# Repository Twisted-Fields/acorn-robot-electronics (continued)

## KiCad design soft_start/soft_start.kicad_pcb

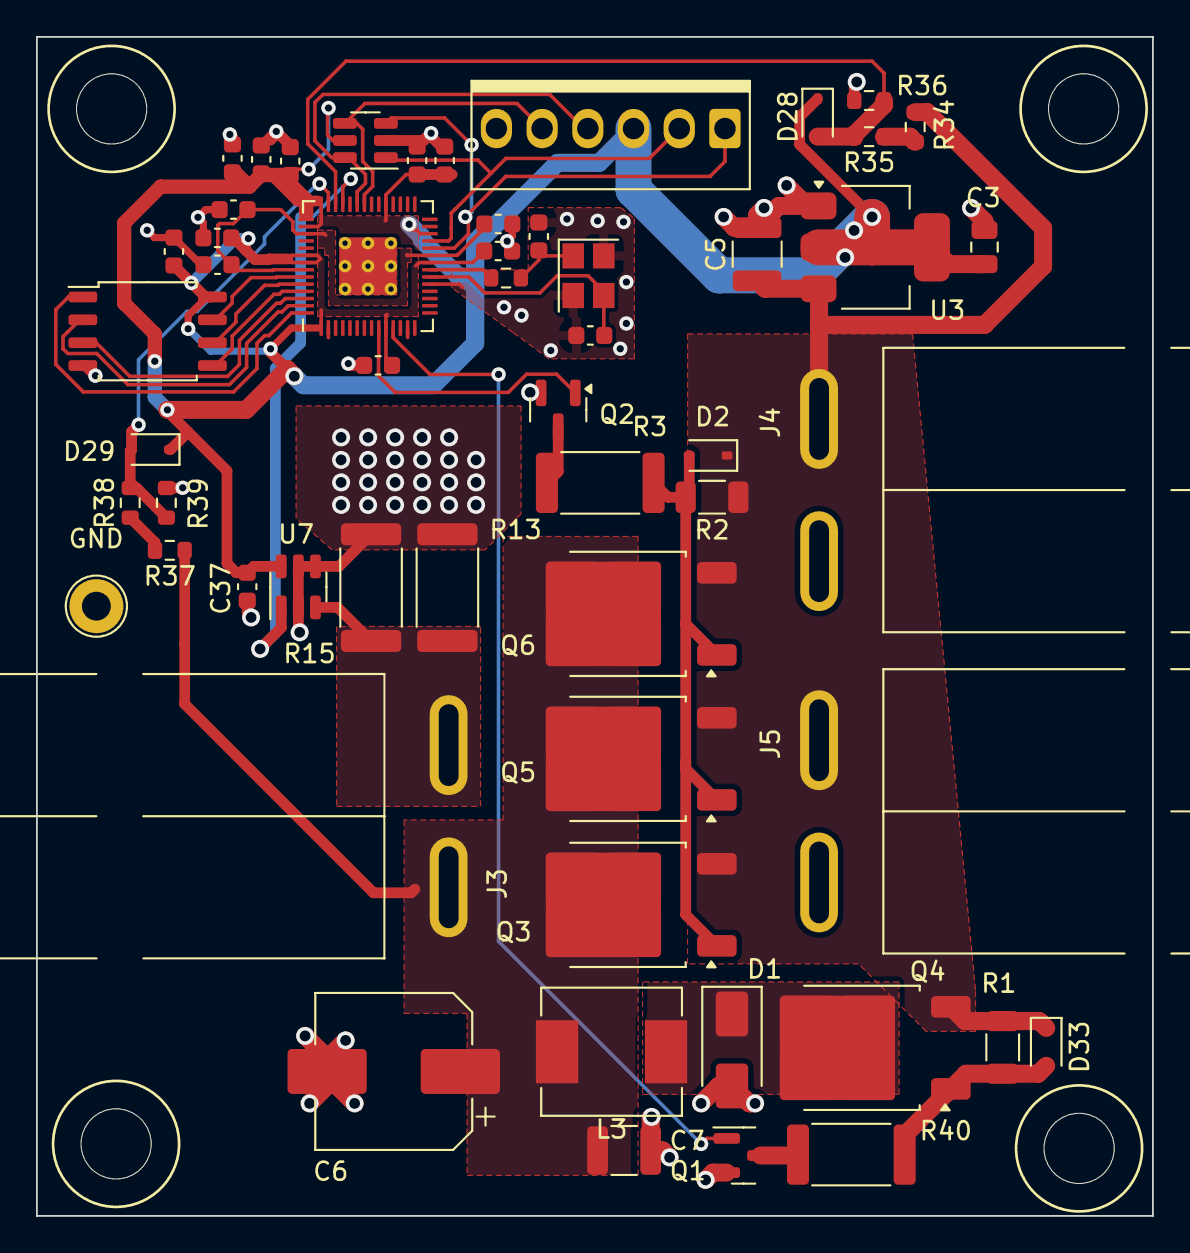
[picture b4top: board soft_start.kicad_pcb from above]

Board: 4 copper layers, 62.0 x 65.5 mm, 59 parts (0 on the bottom side), 31 nets.

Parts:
C1, C2: 20p; C_0603_1608Metric
C3: 10u; C_0805_2012Metric
C4, C14, C15, C29, C30, C31, C33, C34, C35, C36, C37: 100n; C_0603_1608Metric
C5, C7: 4.7uF 100V; C_1210_3225Metric
C6: 47uF 63V solid; CP_Elec_8x10.5
C16, C32: 1u; C_0603_1608Metric
D1: SS310; D_SMA
D2, D33: Zener 10v; D_SOD-323
D28, D29: 1N4148WS; D_SOD-323
H1, H2, H3, H4: MountingHole; MountingHole_3.9mm_Plastite_#6
J2: Conn_01x06; Ckmtw-W-2510S06P_1x06_P2.54mm_Vertical
J3: Power Output; PowerPole_PP45_1336G1_1x2_Horizontal
J4, J5: Conn_01x02; PowerPole_PP45_1336G1_1x2_Horizontal
L3: 47uH; L_Chilisin_BMRB00060612
Q1, Q2: Q_NMOS_GSD; SOT-23
Q3, Q4, Q5, Q6: 100V 34A PMOS; TO-252-2
R1, R2: 10k; R_1206_3216Metric
R3, R40: 2k 2 watt; R_2512_6332Metric
R8: 1.1k; R_0603_1608Metric
R13, R15: 3mΩ; R_2512_6332Metric
R34, R35, R37, R38: 50k 0.1%; R_0603_1608Metric
R36, R39: 5.1k 0.1%; R_0603_1608Metric
TP1: TestPoint; TestPoint_Loop_D2.60mm_Drill1.6mm_Beaded
U1: USBLC6-4SC6; SOT-23-6
U2: W25Q128JVSIQ; SOIC-8_5.23x5.23mm_P1.27mm
U3: LD1117S33TR_SOT223; SOT-223-3_TabPin2
U4: RP2040; RP2040-QFN-56
U7: INA181A2; SOT-23-6
Y1: 12MHz; Crystal_SMD_3225-4Pin_3.2x2.5mm

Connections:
+3V3: C3.1, C4.1, C29.1, C30.1, C31.1, C32.1, C33.1, C34.1, C35.1, C36.1, C37.1, D28.1 (K), D29.1 (K), J2.3, U1.5 (VBUS), U2.8 (VCC), U3.2 (VO), U4.1 (IOVDD), U4.10 (IOVDD), U4.22 (IOVDD), U4.26 (RUN), U4.33 (IOVDD), U4.42 (IOVDD), U4.43 (ADC_AVDD), U4.44 (VREG_IN), U4.48 (USB_VDD), U4.49 (IOVDD), U7.6 (V+)
/1V1: C14.1, C15.1, C16.1, U4.23 (DVDD), U4.45 (VREG_VOUT), U4.50 (DVDD)
/QSPI_SCLK_2: U2.6 (CLK), U4.52 (QSPI_SCLK)
/QSPI_SD0_2: U2.5 (DI(IO0)), U4.53 (QSPI_SD0)
/QSPI_SD1_2: U2.2 (DO(IO1)), U4.55 (QSPI_SD1)
/QSPI_SD2_2: U2.3 (IO2), U4.54 (QSPI_SD2)
/QSPI_SD3_2: U2.7 (IO3), U4.51 (QSPI_SD3)
/QSPI_SS_2: U2.1 (~CS), U4.56 (QSPI_SS)
/RXI_2: J2.4, U1.6 (I/O4), U4.37 (GPIO25)
/SWCLK_2: J2.1, U1.3 (I/O2), U4.24 (SWCLK)
/SWD_2: J2.2, U1.1 (I/O1), U4.25 (SWD)
/TXO_2: J2.5, U1.4 (I/O3), U4.36 (GPIO24)
/V_OUT_P_GATE: D2.2 (A), Q3.1 (G), Q5.1 (G), Q6.1 (G), R2.2, R3.2
CURRENT_MEASURE: U4.39 (GPIO27_ADC1), U7.1
GND: C1.2, C2.2, C3.2, C4.2, C5.2, C6.2, C7.2, C14.2, C15.2, C16.2, C29.2, C30.2, C31.2, C32.2, C33.2, C34.2, C35.2, C36.2, C37.2, D1.2 (A), J2.6, J4.2, J5.2, Q1.2 (S), Q2.2 (S), R13.1, R15.1, R36.2, R39.2, TP1.1, U1.2 (GND), U2.4 (GND), U3.1 (GND), U4.19 (TESTEN), U4.57 (GND), U7.2 (GND), U7.4 (-), U7.5 (REF), Y1.2, Y1.4
unnamed: C2.1, R8.2, Y1.1
unnamed: D1.1 (K), L3.1, Q4.2 (D)
unnamed: D33.2 (A), Q4.1 (G), R1.2, R40.2
unnamed: J3.2, R13.2, R15.2, U7.3 (+)
unnamed: Q1.3 (D), R40.1
unnamed: Q2.3 (D), R3.1
unnamed: R34.2, R35.1
unnamed: R37.2, R38.1
unnamed: C1.1, U4.20 (XIN), Y1.3
unnamed: R8.1, U4.21 (XOUT)
VINPUT: C5.1, D2.1 (K), D33.1 (K), J4.1, J5.1, Q3.3 (S), Q4.3 (S), Q5.3 (S), Q6.3 (S), R1.1, R2.1, R34.1, U3.3 (VI)
VINPUT_MEASURE: D28.2 (A), R35.2, R36.1, U4.40 (GPIO28_ADC2)
VOUT: C6.1, C7.1, J3.1, L3.2, Q3.2 (D), Q5.2 (D), Q6.2 (D), R37.1
VOUT_ENABLE: Q2.1 (G), U4.9 (GPIO7)
VOUT_MEASURE: D29.2 (A), R38.2, R39.1, U4.41 (GPIO29_ADC3)
V_OUT_INDUCTOR: Q1.1 (G), U4.11 (GPIO8)

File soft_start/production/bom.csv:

Designator,Footprint,Quantity,Value,LCSC Part #
"C1, C2",0603,2,20p,C1648
"C14, C15, C29, C30, C31, C33, C34, C35, C36, C37, C4",0603,11,100n,C14663
"C16, C32",0603,2,1u,C15849
C3,0805,1,10u,C15850
"C5, C7",1210,2,4.7uF 100V,C342614
C6,CP_Elec_8x10.5,1,47uF 63V solid,C5246568
D1,D_SMA,1,SS310,C15874
"D2, D33",D_SOD-323,2,Zener 10v,C85383
"D28, D29",D_SOD-323,2,1N4148WS,C2128
J2,Ckmtw-W-2510S06P_1x06_P2.54mm_Vertical,1,Conn_01x06,C140771
J3,PowerPole_PP45_1336G1_1x2_Horizontal,1,Power Output,
"J4, J5",PowerPole_PP45_1336G1_1x2_Horizontal,2,Conn_01x02,
L3,L_Chilisin_BMRB00060612,1,47uH,C5189962
"Q1, Q2",SOT-23,2,Q_NMOS_GSD,C2891566
"Q3, Q4, Q5, Q6",TO-252-2,4,100V 34A PMOS,C2758447
"R1, R2",1206,2,10k,C3013377
"R13, R15",2512,2,3mΩ,C2688862
"R3, R40",2512,2,2k 2 watt,C175463
"R34, R35, R37, R38",0603,4,50k 0.1%,C304067
"R36, R39",0603,2,5.1k 0.1%,C122969
R8,0603,1,1.1k,C22764
TP1,TestPoint_Loop_D2.60mm_Drill1.6mm_Beaded,1,TestPoint,C5199814
U1,SOT-23-6,1,USBLC6-4SC6,C558419
U2,SOIC-8_5.23x5.23mm_P1.27mm,1,W25Q128JVSIQ,C113767
U3,SOT-223-3_TabPin2,1,LD1117S33TR_SOT223,C2845050
U4,RP2040-QFN-56,1,RP2040,C2040
U7,SOT-23-6,1,INA181A2,C2058784
Y1,Crystal_SMD_3225-4Pin_3.2x2.5mm,1,12MHz,C9002

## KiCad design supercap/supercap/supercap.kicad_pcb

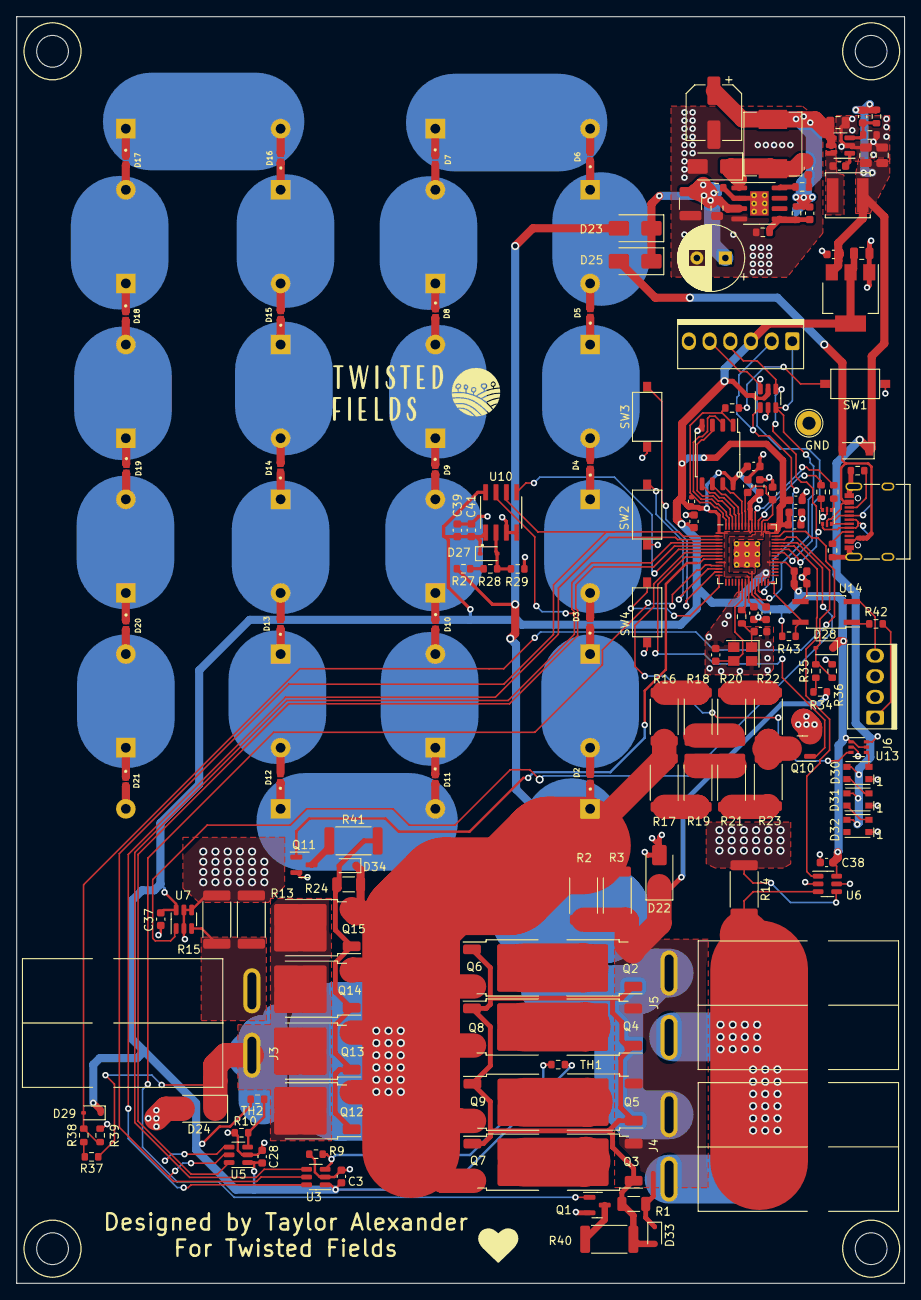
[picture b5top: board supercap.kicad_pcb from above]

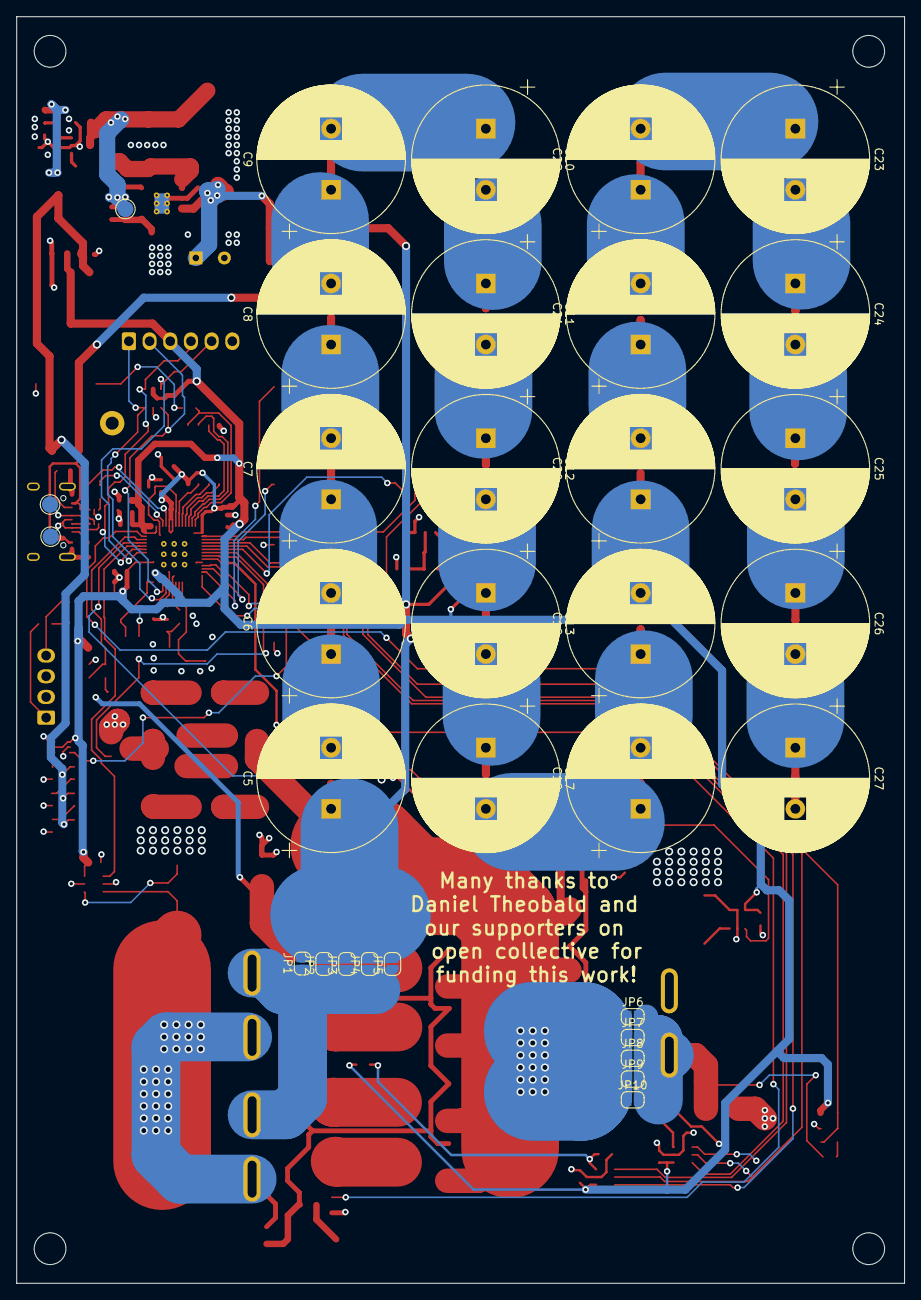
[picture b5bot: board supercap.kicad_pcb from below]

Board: 4 copper layers, 109.0 x 155.5 mm, 192 parts (33 on the bottom side), 105 nets.

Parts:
C1, C2: 20p; C_0603_1608Metric
C3, C16, C28, C32, C39, C45: 1u; C_0603_1608Metric
C4, C14, C15, C29, C30, C31, C33, C34, C35, C36, C37, C38, C41, C47: 100n; C_0603_1608Metric
C5, C6, C7, C8, C9, C10, C11, C12, C13, C17, C18, C19, C20, C21, C22, C23, C24, C25, C26, C27: 120F 2.3v; CP_Radial_D18.0mm_P7.50mm
C40: 47uF 63V solid; CP_Radial_D8.0mm_P3.50mm
C42, C52: 22uF 25V; C_0805_2012Metric
C43: 4.7uF 100V; C_1210_3225Metric
C44: 100nF 100V; C_0805_2012Metric
C46: 22nF; C_0603_1608Metric
C48: 10u; C_0805_2012Metric
C49: 22pF; C_0603_1608Metric
C50: 47uF 10v; C_0805_2012Metric
C51: 47pf; C_0603_1608Metric
C53: 220uF 25V; CP_Elec_6.3x7.7
D1: B5819W SL; D_SOD-123
D2, D3, D4, D5, D6, D7, D8, D9, D10, D11, D12, D13, D14, D15, D16, D17, D18, D19, D20, D21: 2.4v zener; DIO_PESD5V0S1UL_315
D22, D24: SMAJ51A; D_SMA
D23, D25: D; D_SMA
D26: SS310; D_SMA
D27, D28, D29: 1N4148WS; D_SOD-323
D30, D31, D32: WS2812B; LED_WS2812_3528_3.5x2.8mm_P1.5mm
D33, D34: Zener 10v; D_SOD-323
H1, H2, H3, H4: MountingHole; MountingHole_3.9mm_Plastite_#6
J1: CPU2 USB; USB_C_Receptacle_XKB_U262-16XN-4BVC11
J2: Conn_01x06; Ckmtw-W-2510S06P_1x06_P2.54mm_Vertical
J3: Power Output; PowerPole_PP45_1336G1_1x2_Horizontal
J4, J5: Conn_01x02; PowerPole_PP45_1336G1_1x2_Horizontal
J6: CAN2 PLUG; PINREX-744-81-04TW00 _1x04_P2.54mm_Vertical
JP1, JP2, JP3, JP4, JP5, JP6, JP7, JP8, JP9, JP10: SolderJumper_2_Open; SolderJumper-2_P1.3mm_Open_RoundedPad1.0x1.5mm
L1: 10uH; L_Sunlord_SWPA5040S
L2: 47uH; L_Chilisin_BMRB00060612
Q1, Q10, Q11: Q_NMOS_GSD; SOT-23
Q2, Q3, Q4, Q5, Q6, Q7, Q8, Q9, Q12, Q13, Q14, Q15: 100V 34A PMOS; TO-252-2
R1, R24: 10k; R_1206_3216Metric
R2, R3: 1k 2 watt; R_2512_6332Metric
R4, R8: 1.1k; R_0603_1608Metric
R5: DNS; R_0402_1005Metric
R6, R7, R43: 5.1k; R_0603_1608Metric
R9, R10: 10k; R_0603_1608Metric
R11, R12: 27; R_0603_1608Metric
R13, R14, R15: 3mΩ; R_2512_6332Metric
R16, R17, R18, R19, R20, R21, R22, R23: 100R 2W; R_2512_6332Metric
R25: 50mΩ; R_0603_1608Metric
R26: 10Ω; R_0603_1608Metric
R27, R28, R34, R35, R37, R38: 50k 0.1%; R_0603_1608Metric
R29, R36, R39: 5.1k 0.1%; R_0603_1608Metric
R30: 110k 0.1%; R_0603_1608Metric
R31: 15k 0.1%; R_0603_1608Metric
R32: 300k; R_0603_1608Metric
R33: 21.5k; R_0603_1608Metric
R40, R41: 2k 2 watt; R_2512_6332Metric
R42: 120R; R_0603_1608Metric
SW1, SW2, SW3, SW4: SW_MEC_5G; SW_TS_1101_C_W
TH1, TH2: Thermistor 10k; R_0603_1608Metric
TP1: TestPoint; TestPoint_Loop_D2.60mm_Drill1.6mm_Beaded
TP2, TP3, TP4: TestPoint; TestPoint_Pad_D2.0mm
U1: USBLC6-4SC6; SOT-23-6
U2: W25Q128JVSIQ; SOIC-8_5.23x5.23mm_P1.27mm
U3, U5: ADC081S021CISD/NOPB; SOT-23-6
U4: RP2040; RP2040-QFN-56
U6, U7: INA181A2; SOT-23-6
U8: USBLC6-2P6; SOT-666
U9: MT2492; SOT-23-6
U10: ADS7822U; SOIC127P599X175-8N
U11: TX4139; SOIC-8-1EP_3.9x4.9mm_P1.27mm_EP2.29x3mm_ThermalVias
U12: TLV1117LV33DCYR; SOT-223-3_TabPin2
U13: TXS0101DCKR; SOT-363_SC-70-6
U14: EL357N(C)(TA)-G; SO-4_4.4x3.6mm_P2.54mm
Y1: 12MHz; Crystal_SMD_3225-4Pin_3.2x2.5mm

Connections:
5V_ISO_PRESENT: R43.2, U4.28 (GPIO17), U14.4
+3V3: C3.2, C4.1, C28.2, C29.1, C30.1, C31.1, C32.1, C33.1, C34.1, C35.1, C36.1, C37.1, C38.1, C39.2, C41.1, C48.1, D27.1 (K), D28.1 (K), D29.1 (K), J2.3, R5.1, R43.1, TH1.1, TH2.1, U1.5 (VBUS), U2.8 (VCC), U3.1 (VA), U4.1 (IOVDD), U4.10 (IOVDD), U4.22 (IOVDD), U4.26 (RUN), U4.33 (IOVDD), U4.42 (IOVDD), U4.43 (ADC_AVDD), U4.44 (VREG_IN), U4.48 (USB_VDD), U4.49 (IOVDD), U5.1 (VA), U6.6 (V+), U7.6 (V+), U10.1 (VREF), U10.8 (+VCC), U12.2 (VO), U13.1 (VCCA), U13.5 (OE)
+5V: C45.1, C49.1, C50.2, C52.2, D1.1 (K), D30.3 (VDD), D31.3 (VDD), D32.3 (VDD), L1.2, R30.2, U12.3 (VI), U13.6 (VCCB)
+5V_ISO: J6.1, R42.1
+12V: C42.1, C51.1, C53.1, L2.2, R32.2, TP4.1, U9.4 (EN), U9.5 (IN)
/1V1: C14.1, C15.1, C16.1, U4.23 (DVDD), U4.45 (VREG_VOUT), U4.50 (DVDD)
/ADC_CLK: U3.4 (SCLK), U4.4 (GPIO2), U5.4 (SCLK), U10.7 (DCLK)
/ADC_CS1: U3.6 (~CS), U4.3 (GPIO1)
/ADC_CS2: U4.5 (GPIO3), U5.6 (~CS)
/ADC_CS3: U4.6 (GPIO4), U10.5 (~CS/SHDN)
/ADC_DATA: U3.5 (SDATA), U4.2 (GPIO0), U5.5 (SDATA), U10.6 (DOUT)
/BS: R26.1, U11.8 (BS)
/FB: C51.2, R32.1, R33.2, U11.5 (FB)
/LED: U4.7 (GPIO5), U13.3 (A)
/QSPI_SCLK_2: U2.6 (CLK), U4.52 (QSPI_SCLK)
/QSPI_SD0_2: U2.5 (DI(IO0)), U4.53 (QSPI_SD0)
/QSPI_SD1_2: U2.2 (DO(IO1)), U4.55 (QSPI_SD1)
/QSPI_SD2_2: U2.3 (IO2), U4.54 (QSPI_SD2)
/QSPI_SD3_2: U2.7 (IO3), U4.51 (QSPI_SD3)
/QSPI_SS_2: R4.1, R5.2, U2.1 (~CS), U4.56 (QSPI_SS)
/RXI_2: J2.4, U1.4 (I/O3), U4.37 (GPIO25)
/SW: C47.1, D26.1 (K), L2.1, U11.1 (SW)
/SWCLK_2: J2.1, U1.3 (I/O2), U4.24 (SWCLK)
/SWD_2: J2.2, U1.1 (I/O1), U4.25 (SWD)
/TXO_2: J2.5, U1.6 (I/O4), U4.36 (GPIO24)
/USB_DN_2: R12.2, U4.46 (USB_DM)
/USB_DP_2: R11.2, U4.47 (USB_DP)
/USB_D_2+: J1.A6 (D+), J1.B6 (D+), TP3.1, U8.6 (I/O1)
/USB_D_2-: J1.A7 (D-), J1.B7 (D-), TP2.1, U8.4 (I/O2)
/VCAP_GATE: D34.2 (A), Q12.1 (G), Q13.1 (G), Q14.1 (G), Q15.1 (G), R24.2, R41.2
/VINPUT_GATE: D33.2 (A), Q2.1 (G), Q3.1 (G), Q4.1 (G), Q5.1 (G), Q6.1 (G), Q7.1 (G), Q8.1 (G), Q9.1 (G), R1.2, R40.2
/~USB_BOOT_2: R4.2, SW1.2
BLEED_FET: Q10.1 (G), U4.8 (GPIO6)
CURRENT_MEASURE_IN: U4.38 (GPIO26_ADC0), U6.1
CURRENT_MEASURE_OUT: U4.39 (GPIO27_ADC1), U7.1
GND: C1.2, C2.2, C3.1, C4.2, C14.2, C15.2, C16.2, C27.2, C28.1, C29.2, C30.2, C31.2, C32.2, C33.2, C34.2, C35.2, C36.2, C37.2, C38.2, C39.1, C40.2, C41.2, C42.2, C43.2, C44.2, C45.2, C48.2, C50.1, C52.1, C53.2, D21.2 (A), D22.2 (A2), D24.2 (A2), D26.2 (A), D30.1 (GND), D31.1 (GND), D32.1 (GND), J1.A1 (GND), J1.A12 (GND), J1.B1 (GND), J1.B12 (GND), J1.S1 (SHIELD), J2.6, Q1.2 (S), Q10.2 (S), Q11.2 (S), R6.1, R7.2, R9.2, R10.2, R13.1, R14.1, R15.1, R29.2, R31.2, R33.1, R36.2, R39.2, SW1.1, SW2.2, SW3.2, SW4.2, TP1.1, U1.2 (GND), U2.4 (GND), U3.2 (GND), U4.19 (TESTEN), U4.57 (GND), U5.2 (GND), U6.2 (GND), U6.4 (-), U6.5 (REF), U7.2 (GND), U7.4 (-), U7.5 (REF), U8.2 (GND), U9.2 (GND), U10.3 (IN-), U10.4 (GND), U11.4 (GND), U12.1 (GND), U13.2 (GND), U14.3, Y1.2, Y1.4
GND_ISO: J6.4, U14.2
unnamed: C2.1, R8.2, Y1.1
unnamed: C47.2, R26.2
unnamed: C5.2, C6.1, D2.2 (A), D3.1 (K)
unnamed: C6.2, C7.1, D3.2 (A), D4.1 (K)
unnamed: C7.2, C8.1, D4.2 (A), D5.1 (K)
unnamed: C8.2, C9.1, D5.2 (A), D6.1 (K)
unnamed: C9.2, C10.1, D6.2 (A), D7.1 (K)
unnamed: C10.2, C11.1, D7.2 (A), D8.1 (K)
unnamed: C11.2, C12.1, D8.2 (A), D9.1 (K)
unnamed: C13.2, C17.1, D10.2 (A), D11.1 (K)
unnamed: C12.2, C13.1, D9.2 (A), D10.1 (K)
unnamed: C17.2, C18.1, D11.2 (A), D12.1 (K)
unnamed: C18.2, C19.1, D12.2 (A), D13.1 (K)
unnamed: C19.2, C20.1, D13.2 (A), D14.1 (K)
unnamed: C20.2, C21.1, D14.2 (A), D15.1 (K)
unnamed: C21.2, C22.1, D15.2 (A), D16.1 (K)
unnamed: C22.2, C23.1, D16.2 (A), D17.1 (K)
unnamed: C23.2, C24.1, D17.2 (A), D18.1 (K)
unnamed: C24.2, C25.1, D18.2 (A), D19.1 (K)
unnamed: C25.2, C26.1, D19.2 (A), D20.1 (K)
unnamed: C26.2, C27.1, D20.2 (A), D21.1 (K)
unnamed: C40.1, C43.1, C44.1, D23.1 (K), D25.1 (K), R25.2, U11.3 (VIN)
unnamed: D27.2 (A), R28.2, R29.1, U10.2 (IN+)
unnamed: D30.2 (DIN), U13.4 (B)
unnamed: D30.4 (DOUT), D31.2 (DIN)
unnamed: D31.4 (DOUT), D32.2 (DIN)
unnamed: J1.A5 (CC1), R6.2
unnamed: J1.B5 (CC2), R7.1
unnamed: J3.2, R13.2, R15.2, U7.3 (+)
unnamed: J4.2, J5.2, R14.2, U6.3 (+)
unnamed: Q1.3 (D), R40.1
unnamed: Q2.2 (D), Q6.2 (D)
unnamed: Q3.2 (D), Q7.2 (D)
unnamed: Q4.2 (D), Q8.2 (D)
unnamed: Q5.2 (D), Q9.2 (D)
unnamed: Q10.3 (D), R22.2, R23.2
unnamed: Q11.3 (D), R41.1
unnamed: R11.1, U8.1 (I/O1)
unnamed: R12.1, U8.3 (I/O2)
unnamed: R16.2, R18.1
unnamed: R17.2, R19.1
unnamed: R18.2, R20.1
unnamed: R19.2, R21.1
unnamed: R20.2, R22.1
unnamed: R21.2, R23.1
unnamed: R25.1, U11.2 (ILIM), U11.9 (ILIM)
unnamed: R27.2, R28.1
unnamed: R34.2, R35.1
unnamed: R37.2, R38.1
unnamed: R42.2, U14.1
unnamed: R9.1, TH1.2, U3.3 (VIN)
unnamed: SW2.1, U4.12 (GPIO9)
unnamed: SW3.1, U4.13 (GPIO10)
unnamed: SW4.1, U4.14 (GPIO11)
unnamed: C1.1, U4.20 (XIN), Y1.3
unnamed: R8.1, U4.21 (XOUT)
unnamed: R10.1, TH2.2, U5.3 (VIN)
unnamed: C46.1, U9.1 (BS)
unnamed: C49.2, R30.1, R31.1, U9.3 (FB)
unnamed: C46.2, L1.1, U9.6 (SW)
VBUS: D1.2 (A), D25.2 (A), J1.A4 (VBUS), J1.A9 (VBUS), J1.B4 (VBUS), J1.B9 (VBUS), U8.5 (VBUS)
VCAP: C5.1, D2.1 (K), D23.2 (A), D34.1 (K), JP1.2 (B), JP2.2 (B), JP3.2 (B), JP4.2 (B), JP5.2 (B), JP6.1 (A), JP7.1 (A), JP8.1 (A), JP9.1 (A), JP10.1 (A), Q6.3 (S), Q7.3 (S), Q8.3 (S), Q9.3 (S), Q12.3 (S), Q13.3 (S), Q14.3 (S), Q15.3 (S), R2.2, R3.2, R16.1, R17.1, R24.1, R27.1
VINPUT: D22.1 (A1), D33.1 (K), J4.1, J5.1, JP1.1 (A), JP2.1 (A), JP3.1 (A), JP4.1 (A), JP5.1 (A), Q2.3 (S), Q3.3 (S), Q4.3 (S), Q5.3 (S), R1.1, R2.1, R3.1, R34.1
VINPUT_MEASURE: D28.2 (A), R35.2, R36.1, U4.40 (GPIO28_ADC2)
VIN_ENABLE: Q1.1 (G), U4.11 (GPIO8)
VOUT: D24.1 (A1), J3.1, JP6.2 (B), JP7.2 (B), JP8.2 (B), JP9.2 (B), JP10.2 (B), Q12.2 (D), Q13.2 (D), Q14.2 (D), Q15.2 (D), R37.1
VOUT_ENABLE: Q11.1 (G), U4.9 (GPIO7)
VOUT_MEASURE: D29.2 (A), R38.2, R39.1, U4.41 (GPIO29_ADC3)

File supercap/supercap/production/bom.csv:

Designator,Footprint,Quantity,Value,LCSC Part #
"C1, C2",0603,2,20p,C1648
"C10, C11, C12, C13, C17, C18, C19, C20, C21, C22, C23, C24, C25, C26, C27, C5, C6, C7, C8, C9",CP_Radial_D18.0mm_P7.50mm,20,120F 2.3v,
"C14, C15, C29, C30, C31, C33, C34, C35, C36, C37, C38, C4, C41, C47",0603,14,100n,C14663
"C16, C28, C3, C32, C39, C45",0603,6,1u,C15849
C40,CP_Radial_D8.0mm_P3.50mm,1,47uF 63V solid,C2887234
"C42, C52",0805,2,22uF 25V,C602037
C43,1210,1,4.7uF 100V,C342614
C44,0805,1,100nF 100V,C28233
C46,0603,1,22nF,C779971
C48,0805,1,10u,C15850
C49,0603,1,22pF,C1653
C50,0805,1,47uF 10v,C59461
C51,0603,1,47pf,C1671
C53,CP_Elec_6.3x7.7,1,220uF 25V,C340768
D1,D_SOD-123,1,B5819W SL,C8598
"D10, D11, D12, D13, D14, D15, D16, D17, D18, D19, D2, D20, D21, D3, D4, D5, D6, D7, D8, D9",DIO_PESD5V0S1UL_315,20,2.4v zener,C551192
"D22, D24",D_SMA,2,SMAJ51A,C726760
"D23, D25",D_SMA,2,D,C95872
D26,D_SMA,1,SS310,C15874
"D27, D28, D29",D_SOD-323,3,1N4148WS,C2128
"D30, D31, D32",LED_WS2812_3528_3.5x2.8mm_P1.5mm,3,WS2812B,C2890364
"D33, D34",D_SOD-323,2,Zener 10v,C85383
J1,USB_C_Receptacle_XKB_U262-16XN-4BVC11,1,CPU2 USB,C2835315
J2,Ckmtw-W-2510S06P_1x06_P2.54mm_Vertical,1,Conn_01x06,C140771
J3,PowerPole_PP45_1336G1_1x2_Horizontal,1,Power Output,
"J4, J5",PowerPole_PP45_1336G1_1x2_Horizontal,2,Conn_01x02,
J6,PINREX-744-81-04TW00 _1x04_P2.54mm_Vertical,1,CAN2 PLUG,C402777
"JP1, JP10, JP2, JP3, JP4, JP5, JP6, JP7, JP8, JP9",SolderJumper-2_P1.3mm_Open_RoundedPad1.0x1.5mm,10,SolderJumper_2_Open,
L1,L_Sunlord_SWPA5040S,1,10uH,C84608
L2,L_Chilisin_BMRB00060612,1,47uH,C5189962
"Q1, Q10, Q11",SOT-23,3,Q_NMOS_GSD,C2891566
"Q12, Q13, Q14, Q15, Q2, Q3, Q4, Q5, Q6, Q7, Q8, Q9",TO-252-2,12,100V 34A PMOS,C2758447
"R1, R24",1206,2,10k,C3013377
"R10, R9",0603,2,10k,C25804
"R11, R12",0603,2,27,C25190
"R13, R14, R15",2512,3,3mΩ,C2688862
"R16, R17, R18, R19, R20, R21, R22, R23",2512,8,100R 2W,C309610
"R2, R3",2512,2,1k 2 watt,C270948
R25,0603,1,50mΩ,C126169
R26,0603,1,10Ω,C22859
"R27, R28, R34, R35, R37, R38",0603,6,50k 0.1%,C304067
"R29, R36, R39",0603,3,5.1k 0.1%,C122969
R30,0603,1,110k 0.1%,C100721
R31,0603,1,15k 0.1%,C22809
R32,0603,1,300k,C335091
R33,0603,1,21.5k,C705916
"R4, R8",0603,2,1.1k,C22764
"R40, R41",2512,2,2k 2 watt,C175463
R42,0603,1,120R,C22787
"R43, R6, R7",0603,3,5.1k,C23186
"SW1, SW2, SW3, SW4",SW_TS_1101_C_W,4,SW_MEC_5G,C318938
"TH1, TH2",0603,2,Thermistor 10k,C13564
TP1,TestPoint_Loop_D2.60mm_Drill1.6mm_Beaded,1,TestPoint,C5199814
"TP2, TP3, TP4",TestPoint_Pad_D2.0mm,3,TestPoint,
U1,SOT-23-6,1,USBLC6-4SC6,C558419
U10,SOIC127P599X175-8N,1,ADS7822U,C16324
U11,SOIC-8-1EP_3.9x4.9mm_P1.27mm_EP2.29x3mm_ThermalVias,1,TX4139,C329266
U12,SOT-223-3_TabPin2,1,TLV1117LV33DCYR,C15578
U13,SOT-363_SC-70-6,1,TXS0101DCKR,C132031
U14,SO-4_4.4x3.6mm_P2.54mm,1,EL357N(C)(TA)-G,C29981
U2,SOIC-8_5.23x5.23mm_P1.27mm,1,W25Q128JVSIQ,C113767
"U3, U5",SOT-23-6,2,ADC081S021CISD/NOPB,C130227
U4,RP2040-QFN-56,1,RP2040,C2040
"U6, U7",SOT-23-6,2,INA181A2,C2058784
U8,SOT-666,1,USBLC6-2P6,C2827693
U9,SOT-23-6,1,MT2492,C89358
Y1,Crystal_SMD_3225-4Pin_3.2x2.5mm,1,12MHz,C9002

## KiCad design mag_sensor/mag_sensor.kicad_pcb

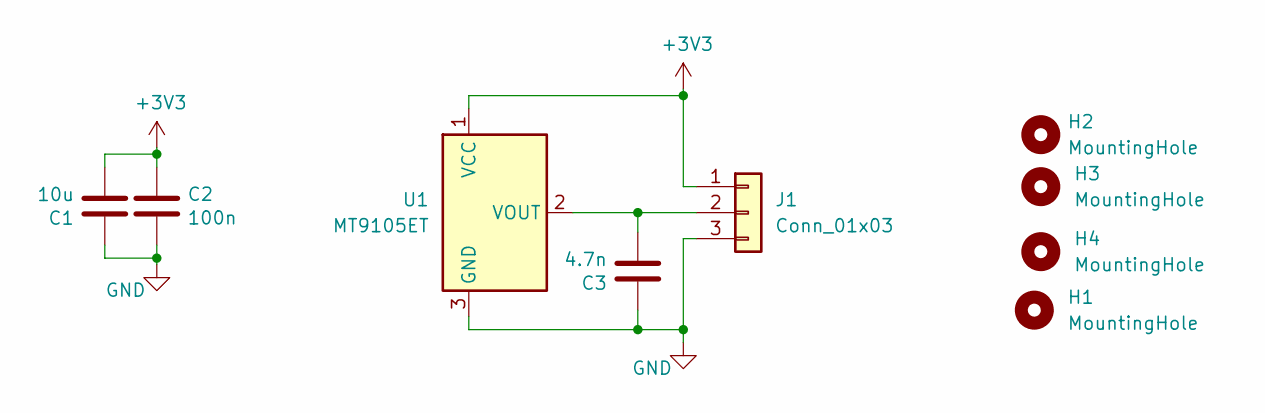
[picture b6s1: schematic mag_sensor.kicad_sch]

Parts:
C1: 10u; C_0805_2012Metric; LCSC C15850
C2: 100n; C_0603_1608Metric; LCSC C14663
C3: 4.7n; C_0603_1608Metric; LCSC C106218
H1, H2, H3, H4: MountingHole; MountingHole_3.9mm_Plastite_#6
J1: Conn_01x03; Molex_KK-254_AE-6410-03A_1x03_P2.54mm_Vertical; LCSC C29275
U1: MT9105ET; SOT-23; LCSC C967861

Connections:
+3V3: C1.2, C2.1, J1.1, U1.1 (VCC)
GND: C1.1, C2.2, C3.1, J1.3, U1.3 (GND)
unnamed: C3.2, J1.2, U1.2 (VOUT)

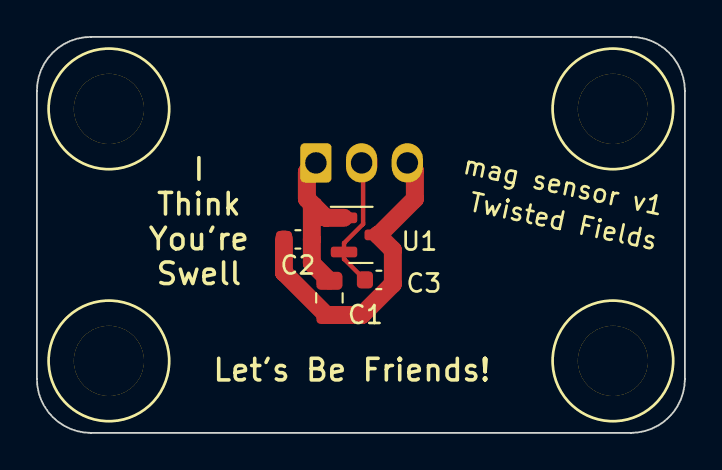
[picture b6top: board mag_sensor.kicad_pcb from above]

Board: 2 copper layers, 36.0 x 22.0 mm, 9 parts (1 on the bottom side), 3 nets.
